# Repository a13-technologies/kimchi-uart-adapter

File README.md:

# kimchi-uart-adapter
UART adapter for the kimichi micro SBC

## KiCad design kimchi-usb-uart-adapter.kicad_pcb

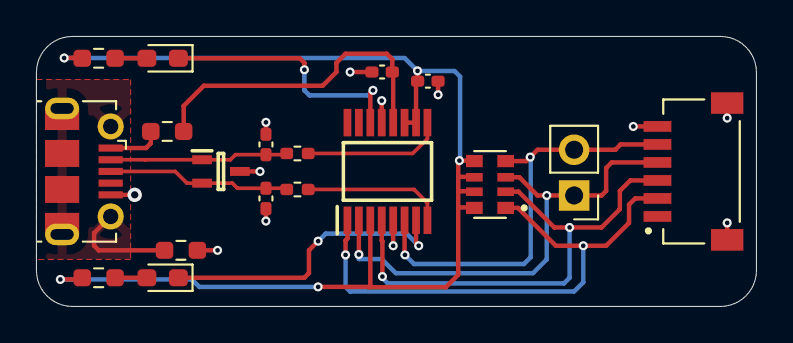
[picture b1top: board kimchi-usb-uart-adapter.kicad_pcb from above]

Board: 2 copper layers, 40.0 x 15.0 mm, 18 parts (0 on the bottom side), 17 nets.

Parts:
C1, C2, C3, C4: C; C_0402_1005Metric_Pad0.74x0.62mm_HandSolder
D1, D2: LED; LED_0603_1608Metric_Pad1.05x0.95mm_HandSolder
D3: AQ3102-02JTG; SOT65P228X110-3N
FB1, FB2: Ferrite_Bead; R_0603_1608Metric_Pad0.98x0.95mm_HandSolder
IC1: FT230XS-R; SOP64P599X175-16N
J1: Conn_01x02; PinHeader_1x02_P2.54mm_Vertical
J2: USB_B_Micro; USB_Micro-B_Molex-105017-0001
J3: SM06B-SRSS-TB(LF)(SN); JST_SM06B-SRSS-TB(LF)(SN)
R1, R2: R; R_0402_1005Metric_Pad0.72x0.64mm_HandSolder
R4, R5: R; R_0603_1608Metric_Pad0.98x0.95mm_HandSolder
RN1: R_Pack04; RESCAXS80P320X160X60-8N

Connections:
+3V3: C2.1, IC1.3, IC1.10, IC1.11, R4.1, R5.1, RN1.5, RN1.6, RN1.7, RN1.8
/CTS: IC1.6, J1.2, J3.5, RN1.4
/D1+: IC1.8, R1.2
/D1-: IC1.9, R2.2
/D+: C3.1, D3.2, J2.3, R1.1
/D-: C4.1, D3.1, J2.2, R2.1
/RTS: IC1.2, J1.1, J3.4, RN1.3
/RX: IC1.4, J3.3, RN1.2
/TX: IC1.1, J3.2, RN1.1
/shield: FB2.1, J2.6
GND: C1.2, C2.2, C3.2, C4.2, D3.3, FB2.2, IC1.5, IC1.13, J2.5, J3.6, J3.S1, J3.S2
unnamed: D1.1, IC1.7
unnamed: D1.2, R4.2
unnamed: D2.1, IC1.14
unnamed: D2.2, R5.2
unnamed: FB1.2, J2.1
VBUS: C1.1, FB1.1, IC1.12

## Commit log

2021-02-22 Board Bringup of the kimichi UART Adapter
    Signed off by: Thore Krug
2021-03-12 Added BOM File
    Signed off by: Thore Krug
